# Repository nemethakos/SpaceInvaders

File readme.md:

# Space Invaders

Space Invaders game for Lab15/[UTAustinX:UT.6.03x Embedded Systems -  Shape the World](https://courses.edx.org/courses/course-v1:UTAustinX+UT.6.03x+1T2016/course/)

### How to compile

Download the zippped source files in any directory in your local machine (Keil 4.x should have been already installed), open the SpaceInvaders.uvproj file and compile the source files.

### The game

The game has 9 levels, each with different types of enemies and bunker arrangement. To save the earth from aliens the player has to defeat all aliens in all levels. Player receives score for all enemies destroyed:
- 10 points for big invader 
- 20 points for middle invader 
- 30 for small invader
- 10 for enemy missiles

For destroying the bonus enemy on the top of the screen, player initially receives a bonus life and 100 points, which doubles after each succesfull attempt. Enemies can destroy the bunkers with multiple shots, but also player can destroy the bunkers by shooting at.
Enemies can also destroy bunkers when they touch them. When enemies reach the earth level the game is over. 

LED1 (red) flashes when an enemy missile is heading for the player. LED2 (green) lights when bonus enemy is on the screen.

### Game strategy

To earn the most points, leave one enemy in each level, and shoot as much bonus enemy as possible. Also shooting the enemy missiles adds 10 points to the player's score.

### Video

https://youtu.be/sHnyJMYgT9Q

### Troubleshooting

In case the game doesn't compile or has runtime errors, please write to akos.space.invaders@gmail.com

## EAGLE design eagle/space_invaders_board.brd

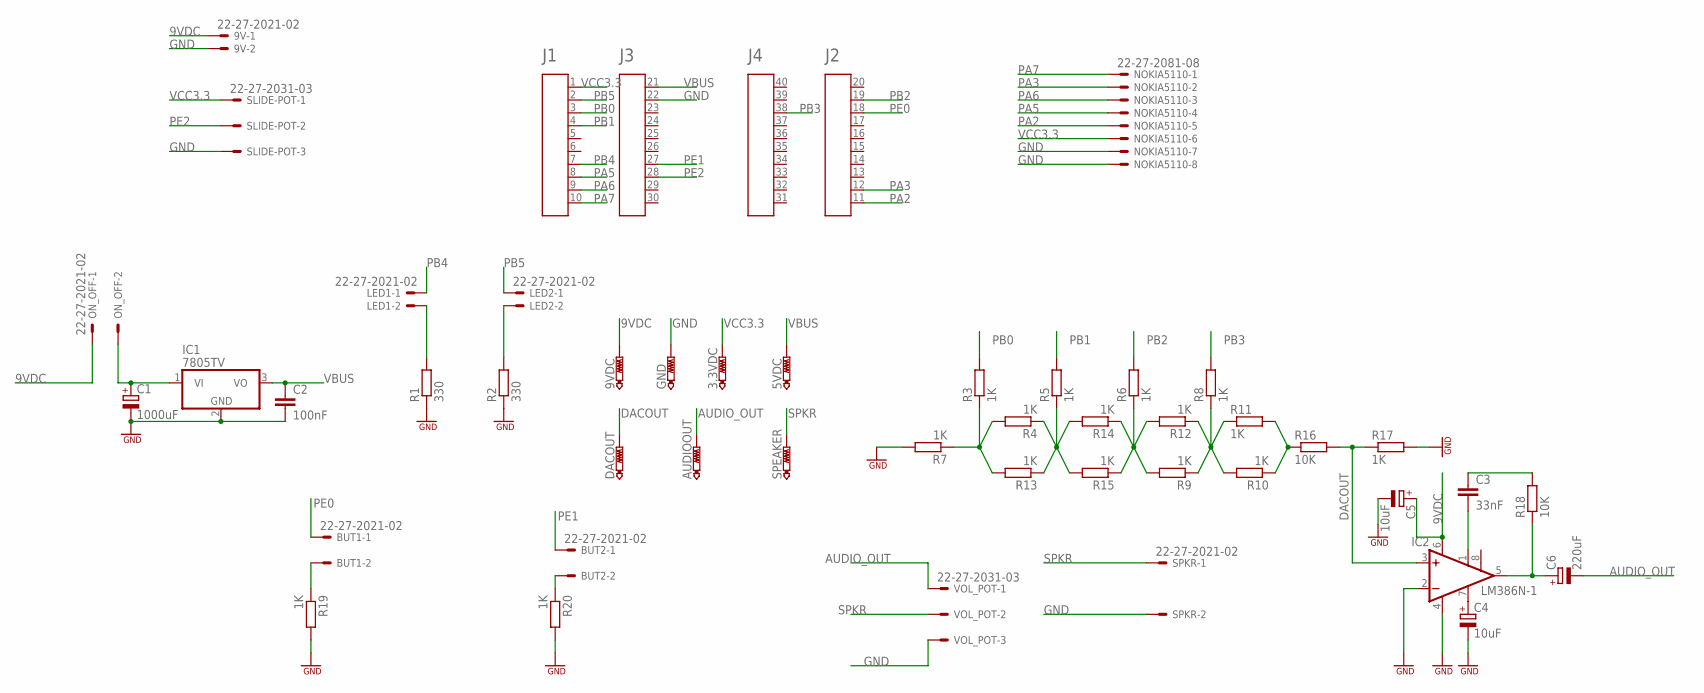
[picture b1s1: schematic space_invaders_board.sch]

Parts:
3.3VDC, 5VDC, 9VDC: PTR1PAD1-13; P1-13
9V: 22-27-2021-02; 6410-02
AUDIOOUT: PTR1PAD1-13; P1-13
BUT1, BUT2: 22-27-2021-02; 6410-02
C1: 1000uF; E5-10,5
C2: 100nF; C025-025X050
C3: 33nF; C2.5-3
C4, C5: 10uF; E2,5-6E
C6: 220uF; E2,5-7
DACOUT: PTR1PAD1-13; P1-13
GND: PTR1PAD1-13; P1-13
IC1: 7805TV; TO220V
IC2: LM386N-1; DIL08
LED1, LED2: 22-27-2021-02; 6410-02
NOKIA5110: 22-27-2081-08; 6410-08
ON_OFF: 22-27-2021-02; 6410-02
R1, R2: 330; 0207/15
R3, R4, R5, R6, R7, R8, R9, R10, R11, R12, R13, R14, R15, R17, R19, R20: 1K; 0207/15
R16, R18: 10K; 0207/15
SLIDE-POT: 22-27-2031-03; 6410-03
SPEAKER: PTR1PAD1-13; P1-13
SPKR: 22-27-2021-02; 6410-02
TIVAC_HEADER: 0; 4X10-BOOSTERPACK
VOL_POT: 22-27-2031-03; 6410-03

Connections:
9VDC: 9V.1, 9VDC.TP, C5.+, IC2.6 (VS), ON_OFF.1
AUDIO_OUT: AUDIOOUT.TP, C6.-, VOL_POT.1
DACOUT: DACOUT.TP, IC2.3 (+IN), R16.2, R17.1
GND: 9V.2, C1.-, C2.2, C4.-, C5.-, GND.TP, IC1.2 (GND), IC2.2 (-IN), IC2.4 (GND), NOKIA5110.7, NOKIA5110.8, R1.1, R2.1, R7.2, R17.2, R19.2, R20.2, SLIDE-POT.3, SPKR.2, TIVAC_HEADER.22, VOL_POT.3
unnamed: R3.1, R4.2, R7.1, R13.2
unnamed: R4.1, R5.1, R13.1, R14.2, R15.2
unnamed: C3.2, IC2.1 (GAIN)
unnamed: LED1.2, R1.2
unnamed: LED2.2, R2.2
unnamed: R6.1, R9.2, R12.2, R14.1, R15.1
unnamed: R8.1, R9.1, R10.2, R11.1, R12.1
unnamed: R10.1, R11.2, R16.1
unnamed: C3.1, R18.2
unnamed: C6.+, IC2.5 (OUT), R18.1
unnamed: C4.+, IC2.7 (BYPASS)
unnamed: C1.+, IC1.1 (VI), ON_OFF.2
unnamed: BUT1.2, R19.1
unnamed: BUT2.2, R20.1
PA2: NOKIA5110.5, TIVAC_HEADER.11
PA3: NOKIA5110.2, TIVAC_HEADER.12
PA5: NOKIA5110.4, TIVAC_HEADER.8
PA6: NOKIA5110.3, TIVAC_HEADER.9
PA7: NOKIA5110.1, TIVAC_HEADER.10
PB0: R3.2, TIVAC_HEADER.3
PB1: R5.2, TIVAC_HEADER.4
PB2: R6.2, TIVAC_HEADER.19
PB3: R8.2, TIVAC_HEADER.38
PB4: LED1.1, TIVAC_HEADER.7
PB5: LED2.1, TIVAC_HEADER.2
PE0: BUT1.1, TIVAC_HEADER.18
PE1: BUT2.1, TIVAC_HEADER.27
PE2: SLIDE-POT.2, TIVAC_HEADER.28
SPKR: SPEAKER.TP, SPKR.1, VOL_POT.2
VBUS: 5VDC.TP, C2.1, IC1.3 (VO), TIVAC_HEADER.21
VCC3.3: 3.3VDC.TP, NOKIA5110.6, SLIDE-POT.1, TIVAC_HEADER.1

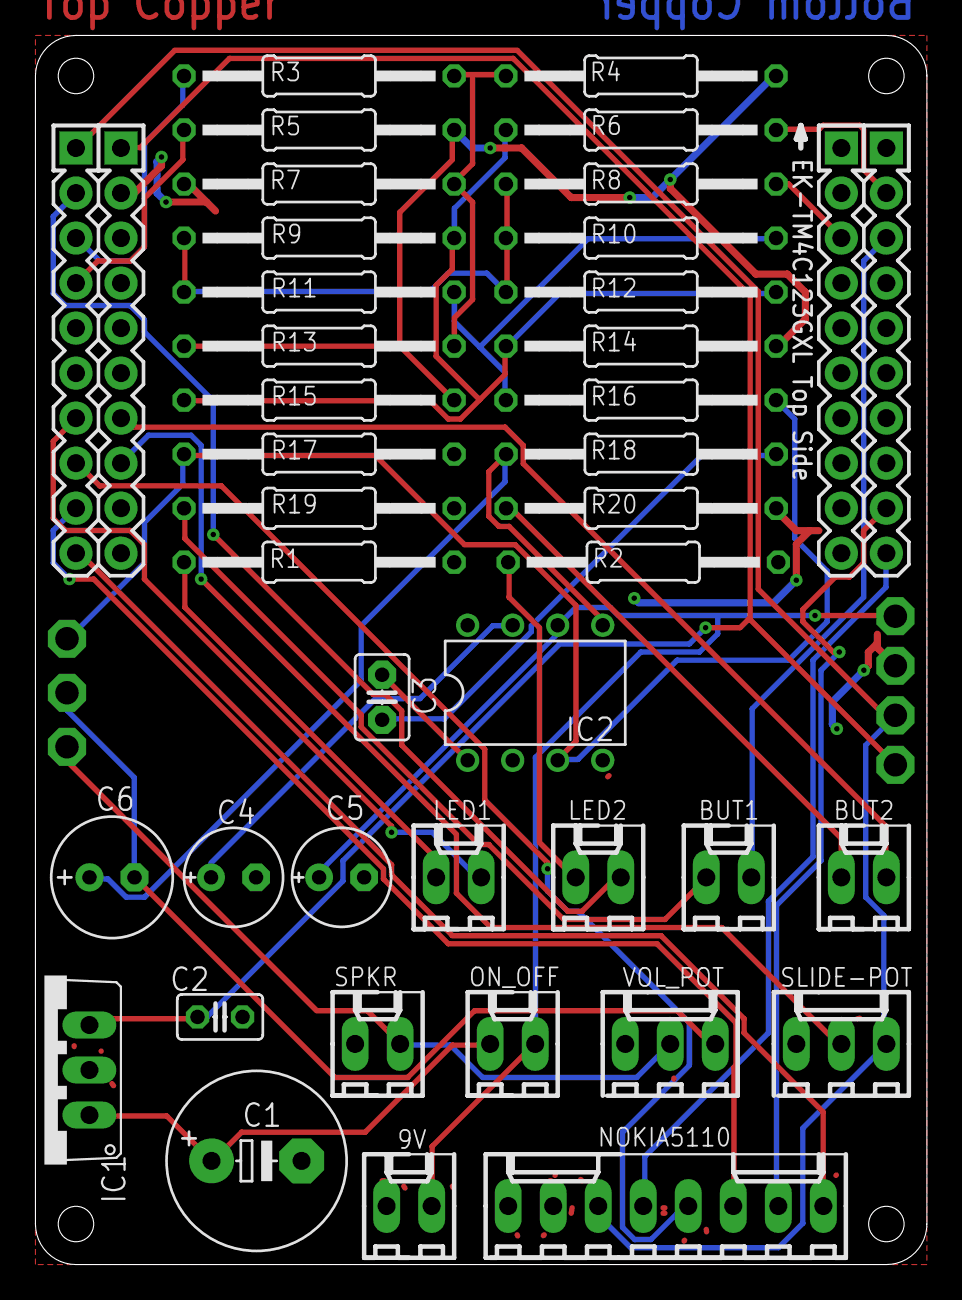
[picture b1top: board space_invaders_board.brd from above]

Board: 2 copper layers, 50.3 x 69.3 mm, 46 parts (0 on the bottom side), 35 nets.

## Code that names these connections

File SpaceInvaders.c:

/**
 * Main file
 * for Space Invaders game for UTAustinX: UT.6.03x Embedded Systems - Shape the World
 * Copyright 2016 by Ákos Németh
 * You may use, edit, run or distribute this file
 * as long as the above copyright notice remains.
 */
// ******* Required Hardware I/O connections*******************
// Slide pot pin 1 connected to ground
// Slide pot pin 2 connected to PE2/AIN1
// Slide pot pin 3 connected to +3.3V
// fire button connected to PE0
// special weapon fire button connected to PE1
// 8*R resistor DAC bit 0 on PB0 (least significant bit)
// 4*R resistor DAC bit 1 on PB1
// 2*R resistor DAC bit 2 on PB2
// 1*R resistor DAC bit 3 on PB3 (most significant bit)
// LED on PB4
// LED on PB5

// Blue Nokia 5110
// ---------------
// Signal        (Nokia 5110) LaunchPad pin
// Reset         (RST, pin 1) connected to PA7
// SSI0Fss       (CE,  pin 2) connected to PA3
// Data/Command  (DC,  pin 3) connected to PA6
// SSI0Tx        (Din, pin 4) connected to PA5
// SSI0Clk       (Clk, pin 5) connected to PA2
// 3.3V          (Vcc, pin 6) power
// back light    (BL,  pin 7) not connected, consists of 4 white LEDs which draw ~80mA total
// Ground        (Gnd, pin 8) ground

// Red SparkFun Nokia 5110 (LCD-10168)
// -----------------------------------
// Signal        (Nokia 5110) LaunchPad pin
// 3.3V          (VCC, pin 1) power
// Ground        (GND, pin 2) ground
// SSI0Fss       (SCE, pin 3) connected to PA3
// Reset         (RST, pin 4) connected to PA7
// Data/Command  (D/C, pin 5) connected to PA6
// SSI0Tx        (DN,  pin 6) connected to PA5
// SSI0Clk       (SCLK, pin 7) connected to PA2
// back light    (LED, pin 8) not connected, consists of 4 white LEDs which draw ~80mA total

#include "ADC.h"
#include "Switch.h"
#include "Sound.h"
#include "Timer2.h"
#include "Controller.h"
#include "TExaS.h"

// function prototypes
void SysTick_Init(unsigned long period);
void PLL_Init(void);


int main(void) {
    TExaS_Init(  NoLCD_NoScope);
    //PLL_Init();
    ADC0_Init();
    Switch_Init(); // PE0, PE1 - input
    Nokia5110_Init();
    Sound_Init();
    SysTick_Init(80000000/30);

    gameLoop();
}

/**
* Updates Player position and button states
*/
void updateInputs() {
    playerX = (ADC0_In()*PLAYER_MAX_X)/ADC_MAX;
    button_fire = Switch_is_Fire_Pushed();
    button_fire_special = Switch_is_Special_Fire_Pushed();
}

// Initialize SysTick interrupts to trigger at 30 Hz
void SysTick_Init(unsigned long period) {
    NVIC_ST_CTRL_R = 0;         // disable SysTick during setup
    NVIC_ST_RELOAD_R = period-1;// reload value
    NVIC_ST_CURRENT_R = 0;      // any write to current clears it
    NVIC_SYS_PRI3_R = (NVIC_SYS_PRI3_R&0x00FFFFFF)|0x20000000; // priority 1
    NVIC_ST_CTRL_R = 0x0007;  // enable SysTick with core clock and interrupts
}

// executes 30Hz
void SysTick_Handler(void) {
    updateInputs();
    TimerCount++;
    Semaphore = 1;
}

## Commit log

2016-04-21 Space Invaders game for UT.6.03x Embedded Systems - Shape the World
    Lab15/Game
2016-04-21 Create gh-pages branch via GitHub
2016-04-22 tm4c123gh6pm.h added to project directory
2016-04-22 Source formatted
2018-07-08 Video thumbnail added
2018-07-08 eagle, gerber and media files added
2018-07-08 Media files
2018-07-09 Create LICENSE
